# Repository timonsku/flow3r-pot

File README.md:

# flow3r-pot

A tool that gives access to a UART port on USB-C SBU pins.
It combines a USB to UART IC and a USB hub to connect both the USB port of the device and the UART itself to the connected USB Host.

The design can be ordered at JLCPCB Assembly service with the included gerber, bom and cpl file.

You can change the IO voltage by placing your own reference voltage LDO on the LDL1117 footprint and cut and re-solder JP1. By default the 3v3 reference is supplied by the CH343P.

The extra IOs from the CH343P are broken out to pin headers. This can be useful if you plan on using this board with other hardware.

While this was developed for the flow3r badge there is nothing inherently specific to that hardware. You can design you own board that places UART on the two SBU pins of your USB-C connector and use this as a debugger for that hardware as well.

Or modify it and put SWD on those pins instead. None of this is USB-C compliant but there is also fairly little to no risk of damaging anything if you were to plug this into a normal device but proceed at your own risk of course. The SBU pins are usually used for either digital audio or analog audio so devices usually will expect voltages up to 3v3 on those pins.

You can also do spicy things like supply an external VBUS via the pin headers.

The 2x USB-A connectors just break out the available extra ports on the USB hub. They are completely optional and are standard USB ports, nothing special about them. Purely for convenience and because we can (and its very cheap).

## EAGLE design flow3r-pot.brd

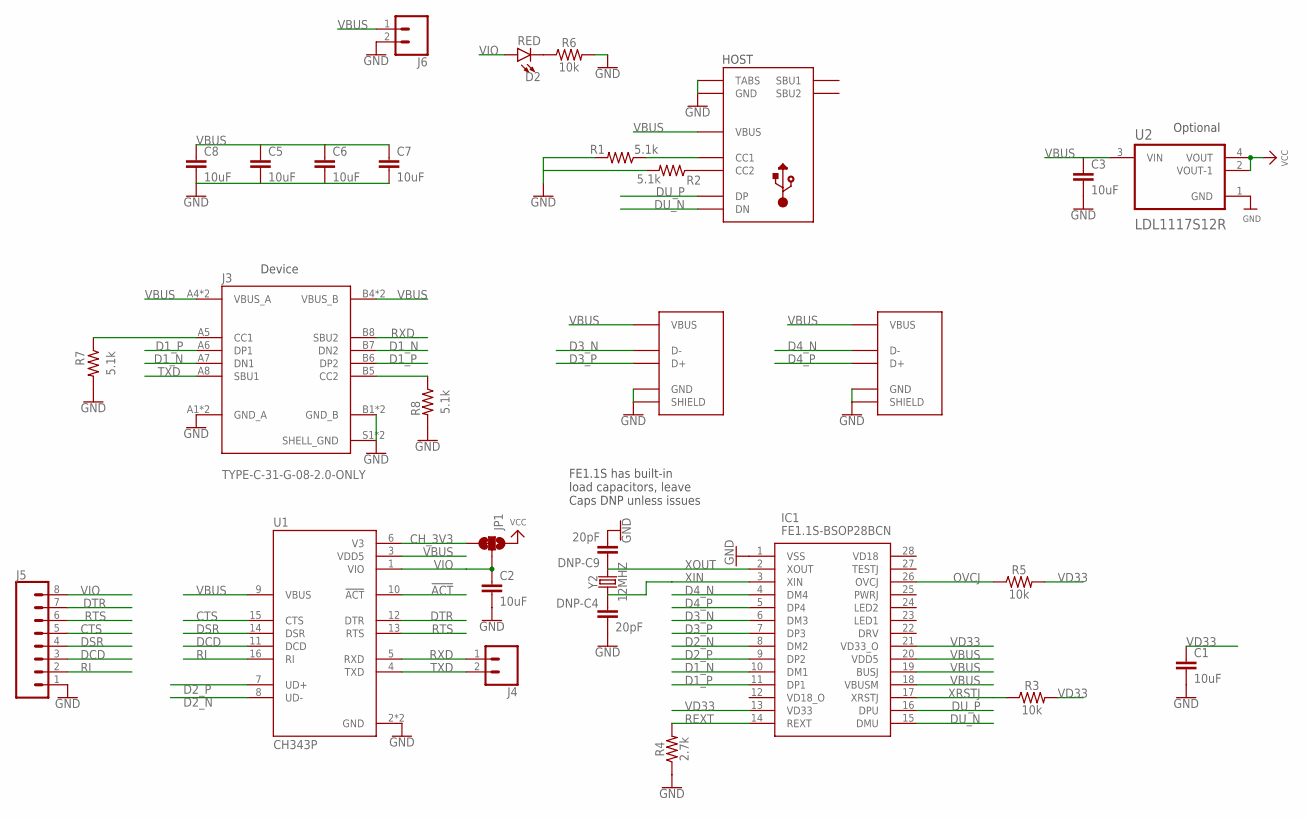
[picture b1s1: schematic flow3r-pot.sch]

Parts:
C1, C2, C3, C5, C6, C7, C8: 10uF; 0603
D2: RED; LED-0603
DNP-C4, DNP-C9: 20pF; 0402-TIGHT
IC1: FE1.1S-BSOP28BCN; SOP64P600X175-28N
J1, J2: JE-USB-A-C42595
J3: TYPE-C-31-G-08-2.0-ONLY
J4, J6: CONN_02; 1X02
J5: CONN_08LOCK_LONGPADS; 1X08_LOCK_LONGPADS
JP1: JUMPER-SMT_3_1-NC_TRACE_NO-SILK; SMT-JUMPER_3_1-NC_TRACE_NO-SILK
R1, R2, R7, R8: 5.1k; 0603
R3, R5, R6: 10k; 0603
R4: 2.7k; 0603
U1: CH343P; QFN50P300X300X80-17N
U2: LDL1117S12R; SOT230P700X180-4N
USB-C-HOST: C709357; USB-TYPE-C_16PIN-MALE-TYPE-C-31-M-12
Y2: 12MHZ; CRYSTAL-SMD-2X2.5MM

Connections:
!ACT: U1.10 (!ACT)
CH_3V3: JP1.3, U1.6 (V3)
CTS: J5.5, U1.15 (CTS)
D1_N: IC1.10 (DM1), J3.A7 (DN1), J3.B7 (DN2)
D1_P: IC1.11 (DP1), J3.A6 (DP1), J3.B6 (DP2)
D2_N: IC1.8 (DM2), U1.8 (UD-)
D2_P: IC1.9 (DP2), U1.7 (UD+)
D3_N: IC1.6 (DM3), J1.D-
D3_P: IC1.7 (DP3), J1.D+
D4_N: IC1.4 (DM4), J2.D-
D4_P: IC1.5 (DP4), J2.D+
DCD: J5.3, U1.11 (DCD)
DSR: J5.4, U1.14 (DSR)
DTR: J5.7, U1.12 (DTR)
DU_N: IC1.15 (DMU), USB-C-HOST.A7 (DN), USB-C-HOST.B7 (DN)
DU_P: IC1.16 (DPU), USB-C-HOST.A6 (DP), USB-C-HOST.B6 (DP)
GND: C1.2, C2.2, C3.2, C5.2, C6.2, C7.2, C8.2, DNP-C4.2, DNP-C9.2, IC1.1 (VSS), J1.GND, J1.SHIELD-1 (SHIELD), J1.SHIELD-2 (SHIELD), J2.GND, J2.SHIELD-1 (SHIELD), J2.SHIELD-2 (SHIELD), J3.A1 (GND_A), J3.A12 (GND_A), J3.B1 (GND_B), J3.B12 (GND_B), J3.S1 (SHELL_GND), J3.S2 (SHELL_GND), J5.1, J6.2, R1.2, R2.2, R4.1, R6.2, R7.2, R8.2, U1.2 (GND), U1.17 (GND), U2.1 (GND), USB-C-HOST.0 (TABS), USB-C-HOST.0-1 (TABS), USB-C-HOST.0-2 (TABS), USB-C-HOST.0-3 (TABS), USB-C-HOST.A1 (GND), USB-C-HOST.A12 (GND), USB-C-HOST.B1 (GND), USB-C-HOST.B12 (GND)
unnamed: R2.1, USB-C-HOST.B5 (CC2)
unnamed: R1.1, USB-C-HOST.A5 (CC1)
unnamed: D2.C, R6.1
unnamed: J3.B5 (CC2), R8.1
unnamed: J3.A5 (CC1), R7.1
OVCJ: IC1.26 (OVCJ), R5.1
REXT: IC1.14 (REXT), R4.2
RI: J5.2, U1.16 (RI)
RTS: J5.6, U1.13 (RTS)
RXD: J3.B8 (SBU2), J4.1, U1.5 (RXD)
TXD: J3.A8 (SBU1), J4.2, U1.4 (TXD)
VBUS: C3.1, C5.1, C6.1, C7.1, C8.1, IC1.18 (VBUSM), IC1.19 (BUSJ), IC1.20 (VDD5), J1.VBUS, J2.VBUS, J3.A4 (VBUS_A), J3.A9 (VBUS_A), J3.B4 (VBUS_B), J3.B9 (VBUS_B), J6.1, U1.3 (VDD5), U1.9 (VBUS), U2.3 (VIN), USB-C-HOST.A4 (VBUS), USB-C-HOST.A9 (VBUS), USB-C-HOST.B4 (VBUS), USB-C-HOST.B9 (VBUS)
VCC: JP1.1, U2.2 (VOUT-1), U2.4 (VOUT)
VD33: C1.1, IC1.13 (VD33), IC1.21 (VD33_O), R3.2, R5.2
VIO: C2.1, D2.A, J5.8, JP1.2, U1.1 (VIO)
XIN: DNP-C4.1, IC1.3 (XIN), Y2.P1 (1)
XOUT: DNP-C9.1, IC1.2 (XOUT), Y2.P3 (2)
XRSTJ: IC1.17 (XRSTJ), R3.1

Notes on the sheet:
HOST
Optional
Device
FE1.1S has built-in load capacitors, leave Caps DNP unless issues

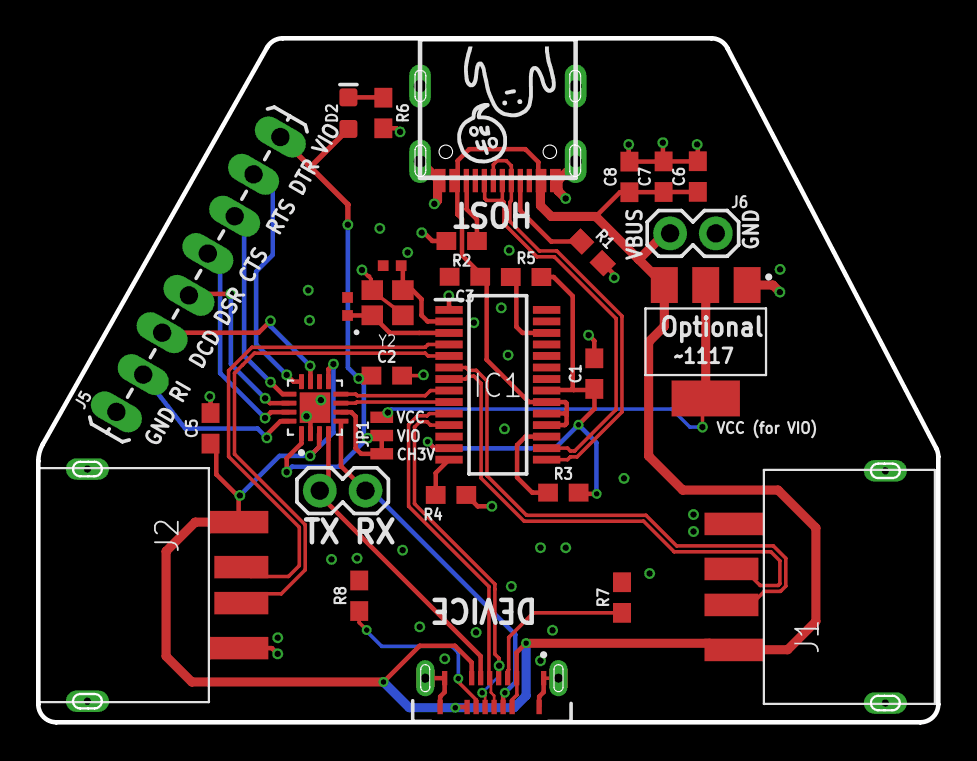
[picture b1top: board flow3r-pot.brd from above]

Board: 2 copper layers, 50.0 x 38.0 mm, 31 parts (0 on the bottom side), 34 nets.

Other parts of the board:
U$2: OHNO-6.5

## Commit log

2023-12-27 add KiCad imports
2023-12-27 add license
2023-12-27 Add image

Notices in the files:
parts and their libraries:
SparkFun-Capacitors: Licensing: Creative Commons ShareAlike 4.0 International - https://creativecommons.org/licenses/by-sa/4.0
Custom-Parts: License: CC-BY-SA
